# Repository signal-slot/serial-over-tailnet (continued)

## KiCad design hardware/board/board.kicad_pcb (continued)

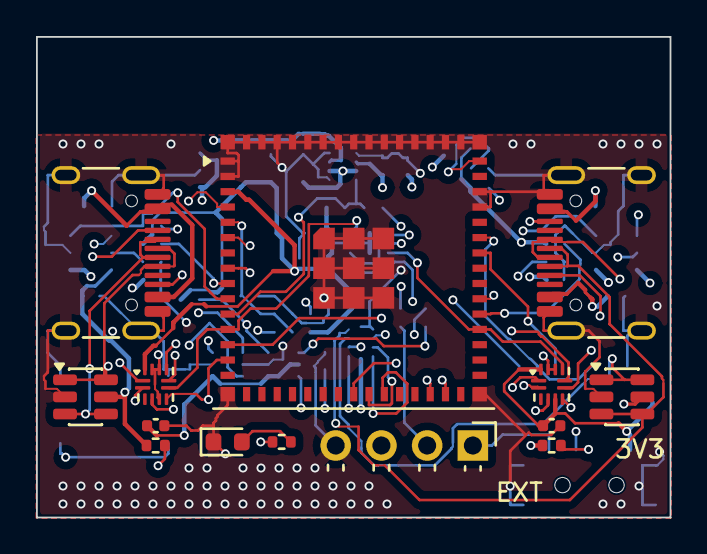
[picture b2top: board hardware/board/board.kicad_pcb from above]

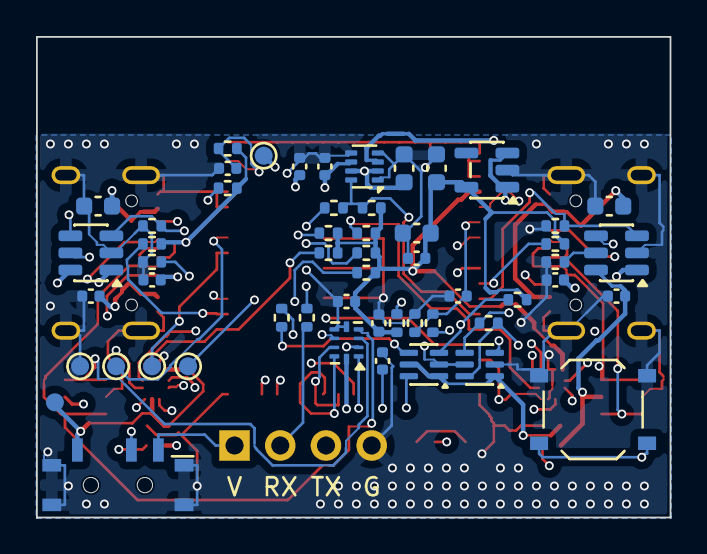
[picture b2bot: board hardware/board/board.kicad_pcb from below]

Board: 4 copper layers, 35.2 x 26.7 mm, 68 parts (54 on the bottom side), 45 nets.

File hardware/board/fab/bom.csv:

Comment,Designator,Footprint,LCSC Part #
ESP32-S3-MINI-1-N4R2,U1,ESP32-S2-MINI-1,C3013941
USB-C A,"J1,J2",USB_C_Receptacle_HRO_TYPE-C-31-M-12,C165948
TUSB320LAI,"U2,U3",Texas_X2QFN-12_1.6x1.6mm_P0.4mm,C132554
LM66200,U4,SOT-583-8,C3235556
AP22653W6,"U5,U6",SOT-23-6,C2158037
TS3USB221,U7,Texas_UQFN-10_1.5x2mm_P0.5mm,C130085
AP2112K-3.3,U8,SOT-23-5,C51118
SN74LVC1T45,"U9,U10",SOT-363_SC-70-6,C9382
USBLC6-2SC6,"U11,U12",SOT-23-6,C7519
UART,J3,PinHeader_1x04_P2.54mm_Horizontal,C32713263
VREF,SW2,MSK12C02,C431540
BOOT,SW1,SW_Push_1P1T_XKB_TS-1187A,C318884
red,D1,LED_0603_1608Metric,C2286
10k,"R1,R2,R11",R_0402_1005Metric,C25744
1u,"C1,C6,C7",C_0402_1005Metric,C52923
22u,C2,C_0603_1608Metric,C59461
100n,"C3,C15,C17,C13,C14,C8,C9,C10,C11,C12,C19",C_0402_1005Metric,C1525
470,R24,R_0402_1005Metric,C25117
10u,"C4,C5",C_0603_1608Metric,C19702
4.7u,"C16,C18",C_0603_1608Metric,C19666
100k,"R10,R12,R13,R14,R15,R20,R25,R21,R22,R23",R_0402_1005Metric,C25741
49.9k,"R16,R17",R_0402_1005Metric,C25897
910k,"R3,R4",R_0402_1005Metric,C25800
4.7k,"R5,R6",R_0402_1005Metric,C25900
200k,"R7,R8,R9",R_0402_1005Metric,C25764
330,"R18,R19",R_0402_1005Metric,C25104

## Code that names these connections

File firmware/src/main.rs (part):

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    #[cfg(feature = "board-adapter")]
    let board = board::Board::init(
        board::Pins {
            mux_sel: peripherals.pins.gpio21,
            vbus_en_a: peripherals.pins.gpio6,
            vbus_en_b: peripherals.pins.gpio40,
            fault_a: peripherals.pins.gpio5,
            fault_b: peripherals.pins.gpio39,
            id_a: peripherals.pins.gpio4,
            id_b: peripherals.pins.gpio38,
            led: peripherals.pins.gpio2,
            vref_sense: peripherals.pins.gpio1,
            adc1: peripherals.adc1,
            pwr_st: peripherals.pins.gpio7,
            i2c0: peripherals.i2c0,
            sda: peripherals.pins.gpio8,
            scl: peripherals.pins.gpio9,
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    // the CDC device in both modes.
    // USB D- and D+: GPIO19/20 on the ESP32-S3, GPIO18/19 on the ESP32-C3.
    #[cfg(not(feature = "board-xiao-c3"))]
    let (usb_dm, usb_dp) = (peripherals.pins.gpio19, peripherals.pins.gpio20);
    #[cfg(feature = "board-xiao-c3")]
    let (usb_dm, usb_dp) = (peripherals.pins.gpio18, peripherals.pins.gpio19);
    let cdc = if setup_mode || cfg!(board_xiao) {
        match console::UsbSerialConsole::install(peripherals.usb_serial, usb_dm, usb_dp) {
            Ok(c) => Some(c),
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    // D9). Set up in both modes, so that its TX line idles high instead of
    // floating into the target's RX.
    #[cfg(feature = "board-adapter")]
    let (uart_tx, uart_rx) = (peripherals.pins.gpio33, peripherals.pins.gpio34);
    // Not D6 and D7, the pins the board labels TX and RX: they are UART0,
    // where the ROM prints at every reset, which a target's boot loader
    // would take for a key press. D10 and D9 sit next to 3V3 and GND, so
    // one 4-pin socket there carries the whole link.
    #[cfg(feature = "board-xiao-s3")]
    let (uart_tx, uart_rx) = (peripherals.pins.gpio9, peripherals.pins.gpio8);
    // The XIAO ESP32C3 keeps TX on D10 (GPIO10) but takes RX on D8 (GPIO8),
    // one pin further: its D9 is GPIO9, which the BOOT button pulls to
    // ground (and which selects download mode if low at reset). GPIO8 is a
    // strapping pin too, but only matters when GPIO9 is low.
    #[cfg(feature = "board-xiao-c3")]
    let (uart_tx, uart_rx) = (peripherals.pins.gpio10, peripherals.pins.gpio8);
    #[cfg(any(feature = "board-adapter", board_xiao))]
    let mut uart_header = Some(
        uart_link::UartSerial::new(
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
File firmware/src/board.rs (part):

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    /// The pins of `hardware/board/design.py`.
    pub struct Pins {
        /// TS3USB221 select: low sends the module's USB to port A, high to port B.
        pub mux_sel: Gpio21<'static>,
        /// LM66200 status: high while port B's VBUS supplies the 5 V.
        pub pwr_st: Gpio7<'static>,
        pub vbus_en_a: Gpio6<'static>,
        pub vbus_en_b: Gpio40<'static>,
        pub fault_a: Gpio5<'static>,
        pub fault_b: Gpio39<'static>,
        pub id_a: Gpio4<'static>,
        pub id_b: Gpio38<'static>,
        pub led: Gpio2<'static>,
        /// Half of VREF, the UART header's voltage (R22 and R23 halve it).
        pub vref_sense: Gpio1<'static>,
        pub adc1: ADC1<'static>,
        pub i2c0: I2C0<'static>,
        pub sda: Gpio8<'static>,
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    struct Lines {
        #[allow(dead_code)]
        mux: PinDriver<'static, Output>,
        vbus_a: PinDriver<'static, Output>,
        vbus_b: PinDriver<'static, Output>,
        pwr_st: PinDriver<'static, Input>,
        fault_a: PinDriver<'static, Input>,
        fault_b: PinDriver<'static, Input>,
        id_a: PinDriver<'static, Input>,
        id_b: PinDriver<'static, Input>,
        #[allow(dead_code)]
        led: PinDriver<'static, Output>,
        vref: VrefSense,
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            // without selecting the GPIO function at the pad, driving them
            // moves nothing. Done for every pin, which costs nothing.
            for pin in [
                pins.mux_sel.pin(),
                pins.pwr_st.pin(),
                pins.vbus_en_a.pin(),
                pins.vbus_en_b.pin(),
                pins.fault_a.pin(),
                pins.fault_b.pin(),
                pins.id_a.pin(),
                pins.id_b.pin(),
                pins.led.pin(),
            ] {
                unsafe { sys::esp_rom_gpio_pad_select_gpio(pin as u32) };
            }
            let pwr_st = PinDriver::input(pins.pwr_st, Pull::Floating)?;
            std::thread::sleep(Duration::from_millis(2));
            let powered_by = if pwr_st.is_high() { Port::B } else { Port::A };
            let target = (!setup_mode).then(|| powered_by.other());
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            // The level is set before the output is enabled, so that the
            // select never passes through the other port on the way (a USB
            // disconnect is seen after 2.5 µs of SE0).
            unsafe { sys::gpio_set_level(pins.mux_sel.pin() as i32, (usb_at == Port::B) as u32) };
            let mux = PinDriver::output(pins.mux_sel)?;
            unsafe {
                sys::gpio_set_level(pins.vbus_en_a.pin() as i32, 0);
                sys::gpio_set_level(pins.vbus_en_b.pin() as i32, 0);
            }
            let vbus_a = PinDriver::output(pins.vbus_en_a)?;
            let vbus_b = PinDriver::output(pins.vbus_en_b)?;
            let mut led = PinDriver::output(pins.led)?;
            led.set_high()?;
            let i2c = I2cDriver::new(
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                vbus_b,
                pwr_st,
                // All four have their pull-ups on the board.
                fault_a: PinDriver::input(pins.fault_a, Pull::Floating)?,
                fault_b: PinDriver::input(pins.fault_b, Pull::Floating)?,
                id_a: PinDriver::input(pins.id_a, Pull::Floating)?,
                id_b: PinDriver::input(pins.id_b, Pull::Floating)?,
                led,
                vref: vref_sense(pins.adc1, pins.vref_sense)?,
                i2c,
            };
            let mut state = State::default();
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        TickType::from(Duration::from_millis(I2C_TIMEOUT_MS)).0
    }

    fn vref_sense(adc1: ADC1<'static>, pin: Gpio1<'static>) -> Result<VrefSense> {
        let adc = AdcDriver::new(adc1)?;
        let config = AdcChannelConfig {
            attenuation: attenuation::DB_12,
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
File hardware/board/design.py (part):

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    ("U11", "Power_Protection:USBLC6-2SC6", "USBLC6-2SC6", "Package_TO_SOT_SMD:SOT-23-6", "C7519", usblc6("A")),
    ("U12", "Power_Protection:USBLC6-2SC6", "USBLC6-2SC6", "Package_TO_SOT_SMD:SOT-23-6", "C7519", usblc6("B")),
    ("J3", "Connector_Generic:Conn_01x04", "UART", "Connector_PinHeader_2.54mm:PinHeader_1x04_P2.54mm_Horizontal", "C32713263",
     {"4": "GND", "3": "J3_TX", "2": "J3_RX", "1": "VREF_EXT"}),   # pin 1 is the right-hand hole
    # VREF, the target side's supply of the level translators: the header's VREF pin, or
    # 3.3 V for a target wired with three wires only (GND, TX, RX). The common contact is
    # pin 2, the tabs are the cover.
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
